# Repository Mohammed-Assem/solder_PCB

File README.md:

# solder_PCB

## Description
This project is a simple PCB circuit designed in **KiCad** where 3 LEDs are controlled individually — 3 by push buttons, and 1 by a **light-dependent resistor (LDR)** instead of a regular resistor. The LDR allows the LED to light up automatically in the dark, acting like a simple light sensor.
---

## 🧰 Bill of Materials (BOM)

| Component        | Quantity | Description                        |
|------------------|----------|------------------------------------|
| Resistor (220Ω)  | 2        | For current limiting (LEDs)        |
| LDR              | 1        | Replaces 1 resistor for light control |
| LED              | 3        | Any color                          |
| Push Button      | 2        | THT push button                    |
| Battery Holder   | 1        | For 9V or coin cell                |
| Battery          | 1        | 9V or CR2032                       |
| PCB              | 1        | Designed in KiCad                  |

---

## Screenshots

### Schematic  

### PCB Layout  

### 3D View  

---

## ⚙️ How it Works

- **LED 1**: Controlled by push button 1  
- **LED 2**:  Controlled by **LDR** — it lights up in darkness!
- **LED 3**: Controlled by push button 2 

This makes it not only a manual control circuit but also a **light-reactive system**.

---

## 💬 Slack Username
`@Mohamed Assem`

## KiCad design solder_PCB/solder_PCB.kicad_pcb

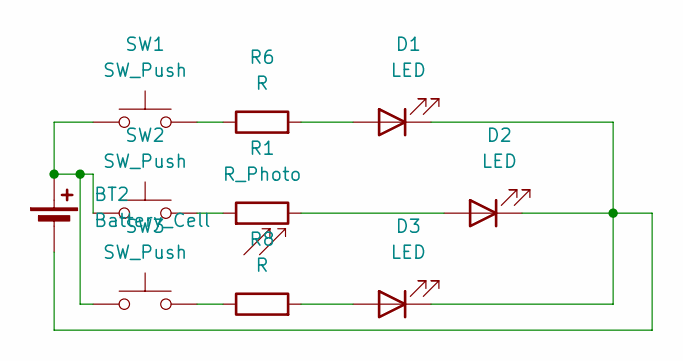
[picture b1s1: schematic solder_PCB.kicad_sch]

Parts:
BT2: Battery_Cell; BatteryHolder_Keystone_3034_1x20mm
D1, D2, D3: LED; LED_D5.0mm
R1: R_Photo; R_LDR_5.1x4.3mm_P3.4mm_Vertical
R6, R8: R; R_Axial_DIN0207_L6.3mm_D2.5mm_P7.62mm_Horizontal
SW1, SW2, SW3: SW_Push; SW_PUSH_6mm

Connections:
unnamed: BT2.1 (+), SW1.1, SW2.1, SW3.1
unnamed: BT2.2 (-), D1.1 (K), D2.1 (K), D3.1 (K)
unnamed: D1.2 (A), R6.2
unnamed: D2.2 (A), R1.2
unnamed: D3.2 (A), R8.2
unnamed: R1.1, SW2.2
unnamed: R6.1, SW1.2
unnamed: R8.1, SW3.2

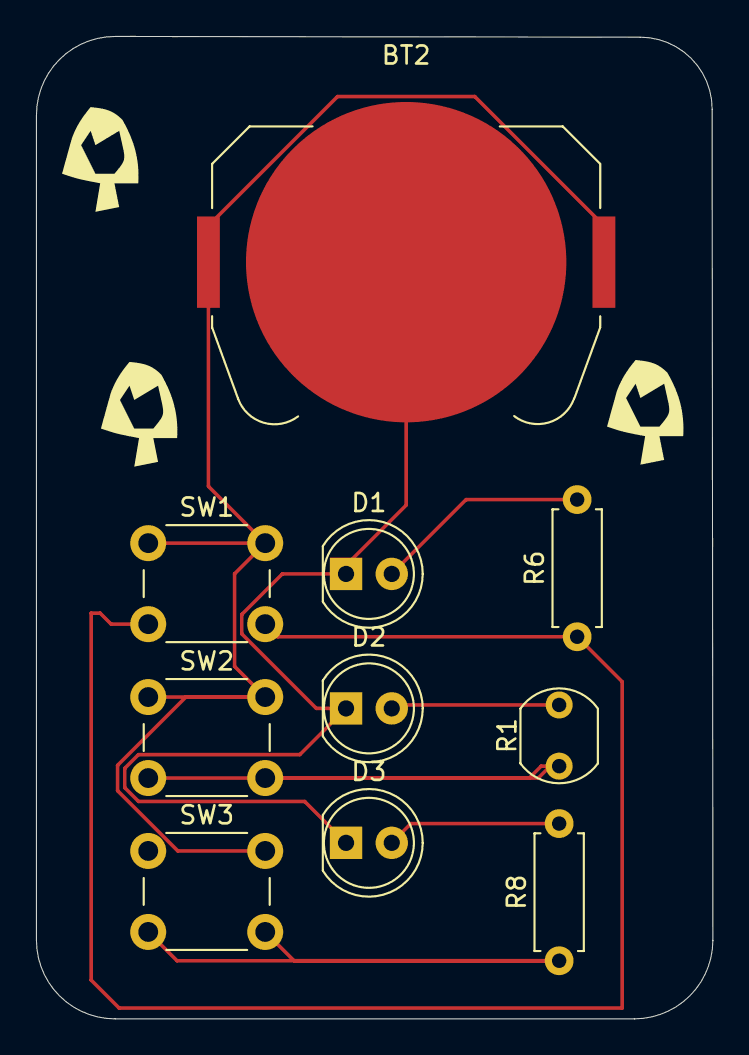
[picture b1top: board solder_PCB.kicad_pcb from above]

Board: 2 copper layers, 37.6 x 54.6 mm, 10 parts (0 on the bottom side), 8 nets.
